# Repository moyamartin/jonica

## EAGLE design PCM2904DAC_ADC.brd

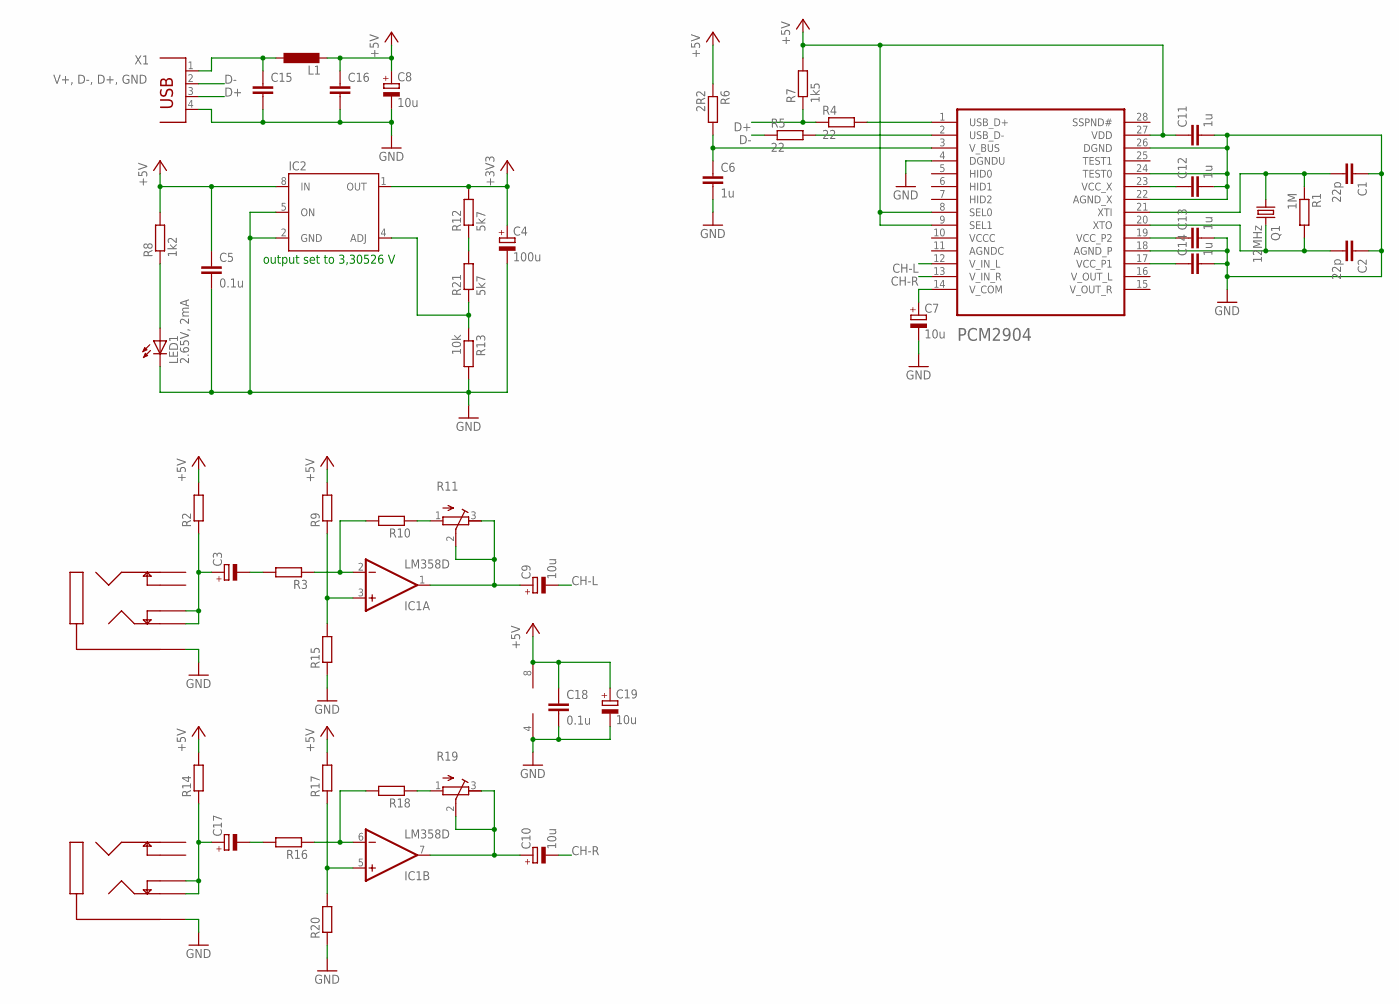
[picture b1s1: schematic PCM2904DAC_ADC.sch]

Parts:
C1, C2: 22p; C1206
C3, C17: CPOL-EU153CLV-0505; 153CLV-0505
C4: 100u; 153CLV-0807
C5, C18: 0.1u; C1206
C6, C11, C12, C13, C14: 1u; C1206
C7, C8, C9, C10, C19: 10u; 153CLV-0505
C15, C16: C-EUC1206K; C1206K
IC1: LM358D; SO08
IC2: LM2931-ADJM; SO08
L1: L-EU0207/7; 0207/7
LED1: 2.65V, 2mA; CHIPLED_0805
PCM2904: PCM2904; SSOP28
Q1: 12MHz; HC49U-V
R1: 1M; R1206
R2, R3, R9, R10, R14, R15, R16, R17, R18, R20: R-EU_R1206W; R1206W
R4, R5: 22; R1206
R6: 2R2; R1206
R7: 1k5; R1206
R8: 1k2; R1206
R11, R19: R-TRIMM64W; RTRIM64W
R12, R21: 5k7; R1206
R13: 10k; R1206
U$1, U$8: 1/8STEREO
X1: V+, D-, D+, GND; PN61729

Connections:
+3V3: C4.+, IC2.1 (OUT), R12.2
+5V: C5.1, C8.+, C11.1, C16.1, C18.1, C19.+, IC1.8 (V+), IC2.8 (IN), L1.2, PCM2904.8 (SEL0), PCM2904.9 (SEL1), PCM2904.27 (VDD), R2.2, R6.1, R7.2, R8.2, R9.2, R14.2, R17.2
CH-L: C9.-, PCM2904.12 (V_IN_L)
CH-R: C10.-, PCM2904.13 (V_IN_R)
D+: R4.1, R7.1, X1.3
D-: R5.1, X1.2
GND: C1.1, C2.1, C4.-, C5.2, C6.2, C7.-, C8.-, C11.2, C12.2, C13.2, C14.2, C15.2, C16.2, C18.2, C19.-, IC1.4 (V-), IC2.2 (GND), IC2.5 (ON), LED1.C, PCM2904.4 (DGNDU), PCM2904.18 (AGND_P), PCM2904.22 (AGND_X), PCM2904.24 (TEST0), PCM2904.26 (DGND), R13.2, R15.1, R20.1, U$1.P$1, U$8.P$1, X1.4
unnamed: C1.2, PCM2904.21 (XTI), Q1.1, R1.1
unnamed: C2.2, PCM2904.20 (XTO), Q1.2, R1.2
unnamed: PCM2904.1 (USB_D+), R4.2
unnamed: C3.+, R2.1, U$8.P$4, U$8.P$5
unnamed: PCM2904.2 (USB_D-), R5.2
unnamed: C17.+, R14.1, U$1.P$4, U$1.P$5
unnamed: C15.1, L1.1, X1.1
unnamed: C17.-, R16.2
unnamed: IC1.6 (-IN), R16.1, R18.2
unnamed: C6.1, PCM2904.3 (V_BUS), R6.2
unnamed: R18.1, R19.1 (A)
unnamed: C3.-, R3.2
unnamed: C10.+, IC1.7 (OUT), R19.2 (S), R19.3 (E)
unnamed: IC1.2 (-IN), R3.1, R10.2
unnamed: C7.+, PCM2904.14 (V_COM)
unnamed: R10.1, R11.1 (A)
unnamed: C9.+, IC1.1 (OUT), R11.2 (S), R11.3 (E)
unnamed: IC1.3 (+IN), R9.1, R15.2
unnamed: C14.1, PCM2904.17 (VCC_P1)
unnamed: C13.1, PCM2904.19 (VCC_P2)
unnamed: IC1.5 (+IN), R17.1, R20.2
unnamed: R12.1, R21.2
unnamed: C12.1, PCM2904.23 (VCC_X)
unnamed: LED1.A, R8.1
unnamed: IC2.4 (ADJ), R13.1, R21.1

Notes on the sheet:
output set to 3,30526 V

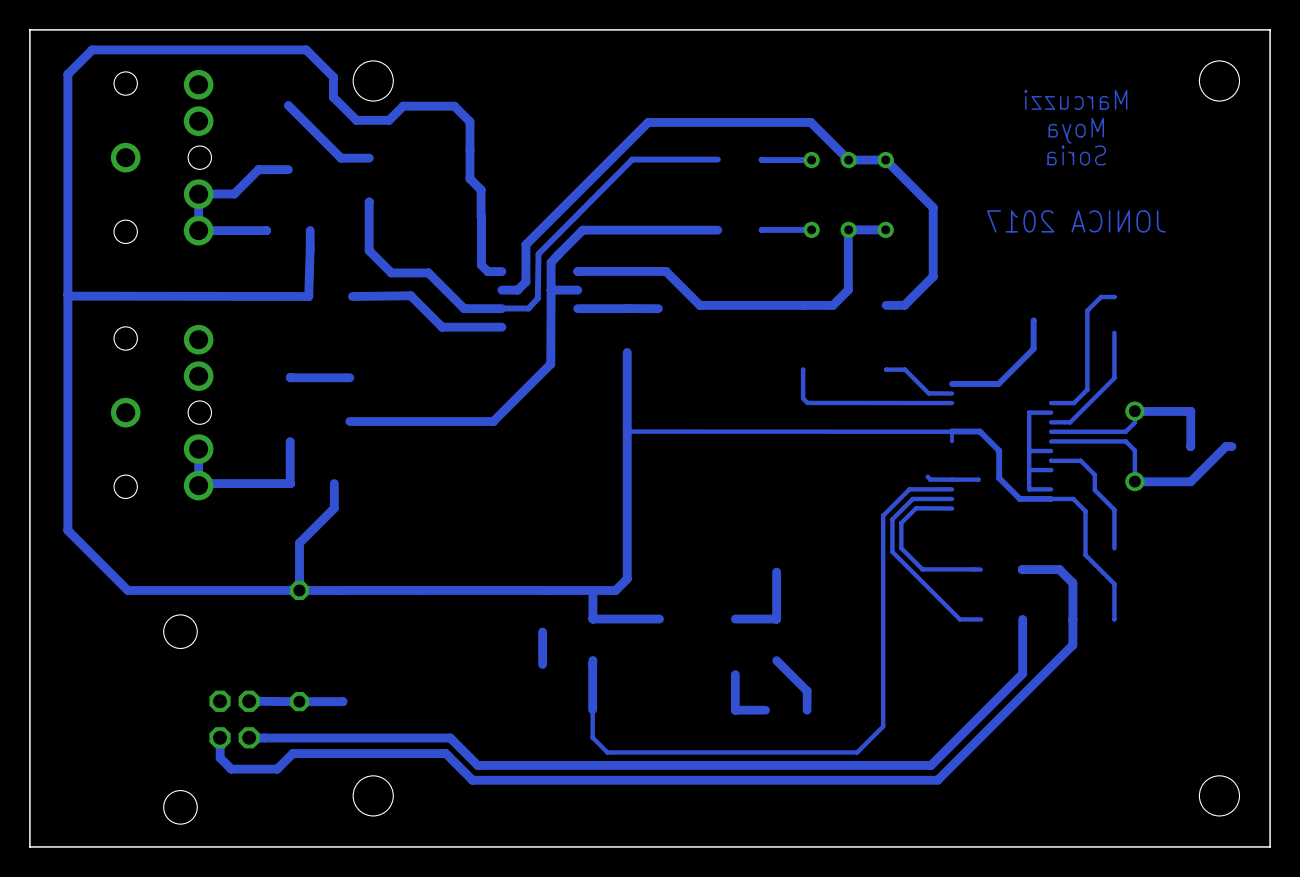
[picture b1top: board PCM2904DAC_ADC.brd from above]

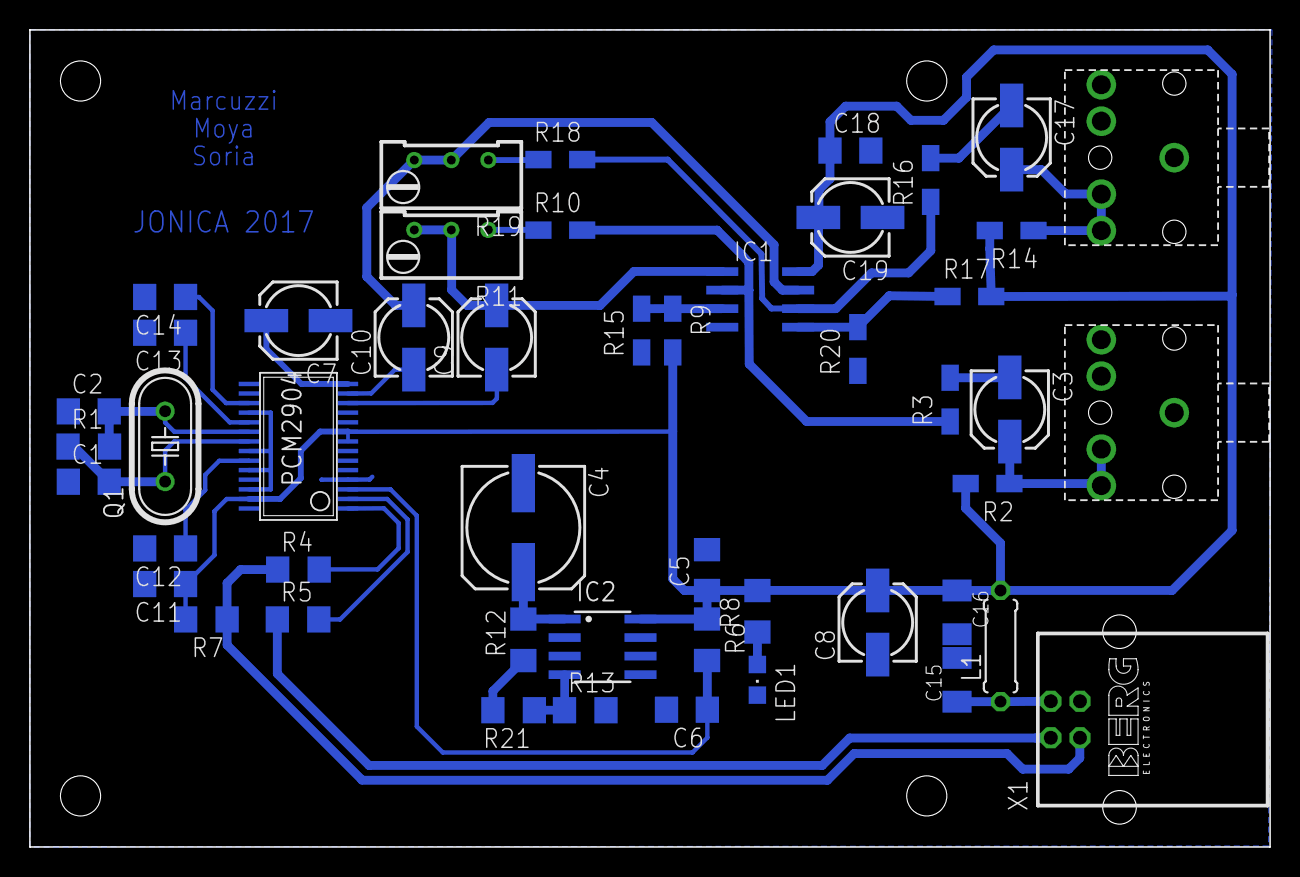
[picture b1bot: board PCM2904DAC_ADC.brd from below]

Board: 2 copper layers, 85.0 x 56.0 mm, 49 parts (49 on the bottom side), 32 nets.

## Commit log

2017-10-08 Adaptación PCM2904 a rPi - Hat
2017-10-09 Agregados etapas preamplificadoras...
    ... y cambiado el ordenamiento y routeo de pistas
2017-10-09 Commit adicional
2017-10-09 movi un poco las cosas de lugar, para que el plano de masa no se corte
2017-10-09 Mas cosas
2017-10-10 cambiado tamaño del led, fichas stereo, y otras cosas sueltas
2017-10-10 Pasado todo a la capa bottom.
    No le cambié el usb porque había que rediseñar la pcb y ando con poco
    tiempo, si quieren lo vemos dps!
    Salu2
2017-10-10 Modificada posicion de un cap
2017-10-10 mas cambios
2017-10-10 Generado PDF de la capa bottom
2017-10-10 agregada R de 100 ohms en el sch. FALTA ACOMODARLA EN EL PCB
2017-10-11 Mirror + R 100 Ohms
2017-10-11 Fixed
2017-10-14 Codigo Prueba
2017-10-17 Todos los archivos
2017-10-17 Revert "Todos los archivos"
    This reverts commit 7457c163f9289e5addb9e13f31f6b2f11749d37e.
